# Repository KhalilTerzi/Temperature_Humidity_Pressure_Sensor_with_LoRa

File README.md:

# Temperature_Humidity_Pressure_Sensor_with_LoRa
Intelligent Sensor Connected with LoRa

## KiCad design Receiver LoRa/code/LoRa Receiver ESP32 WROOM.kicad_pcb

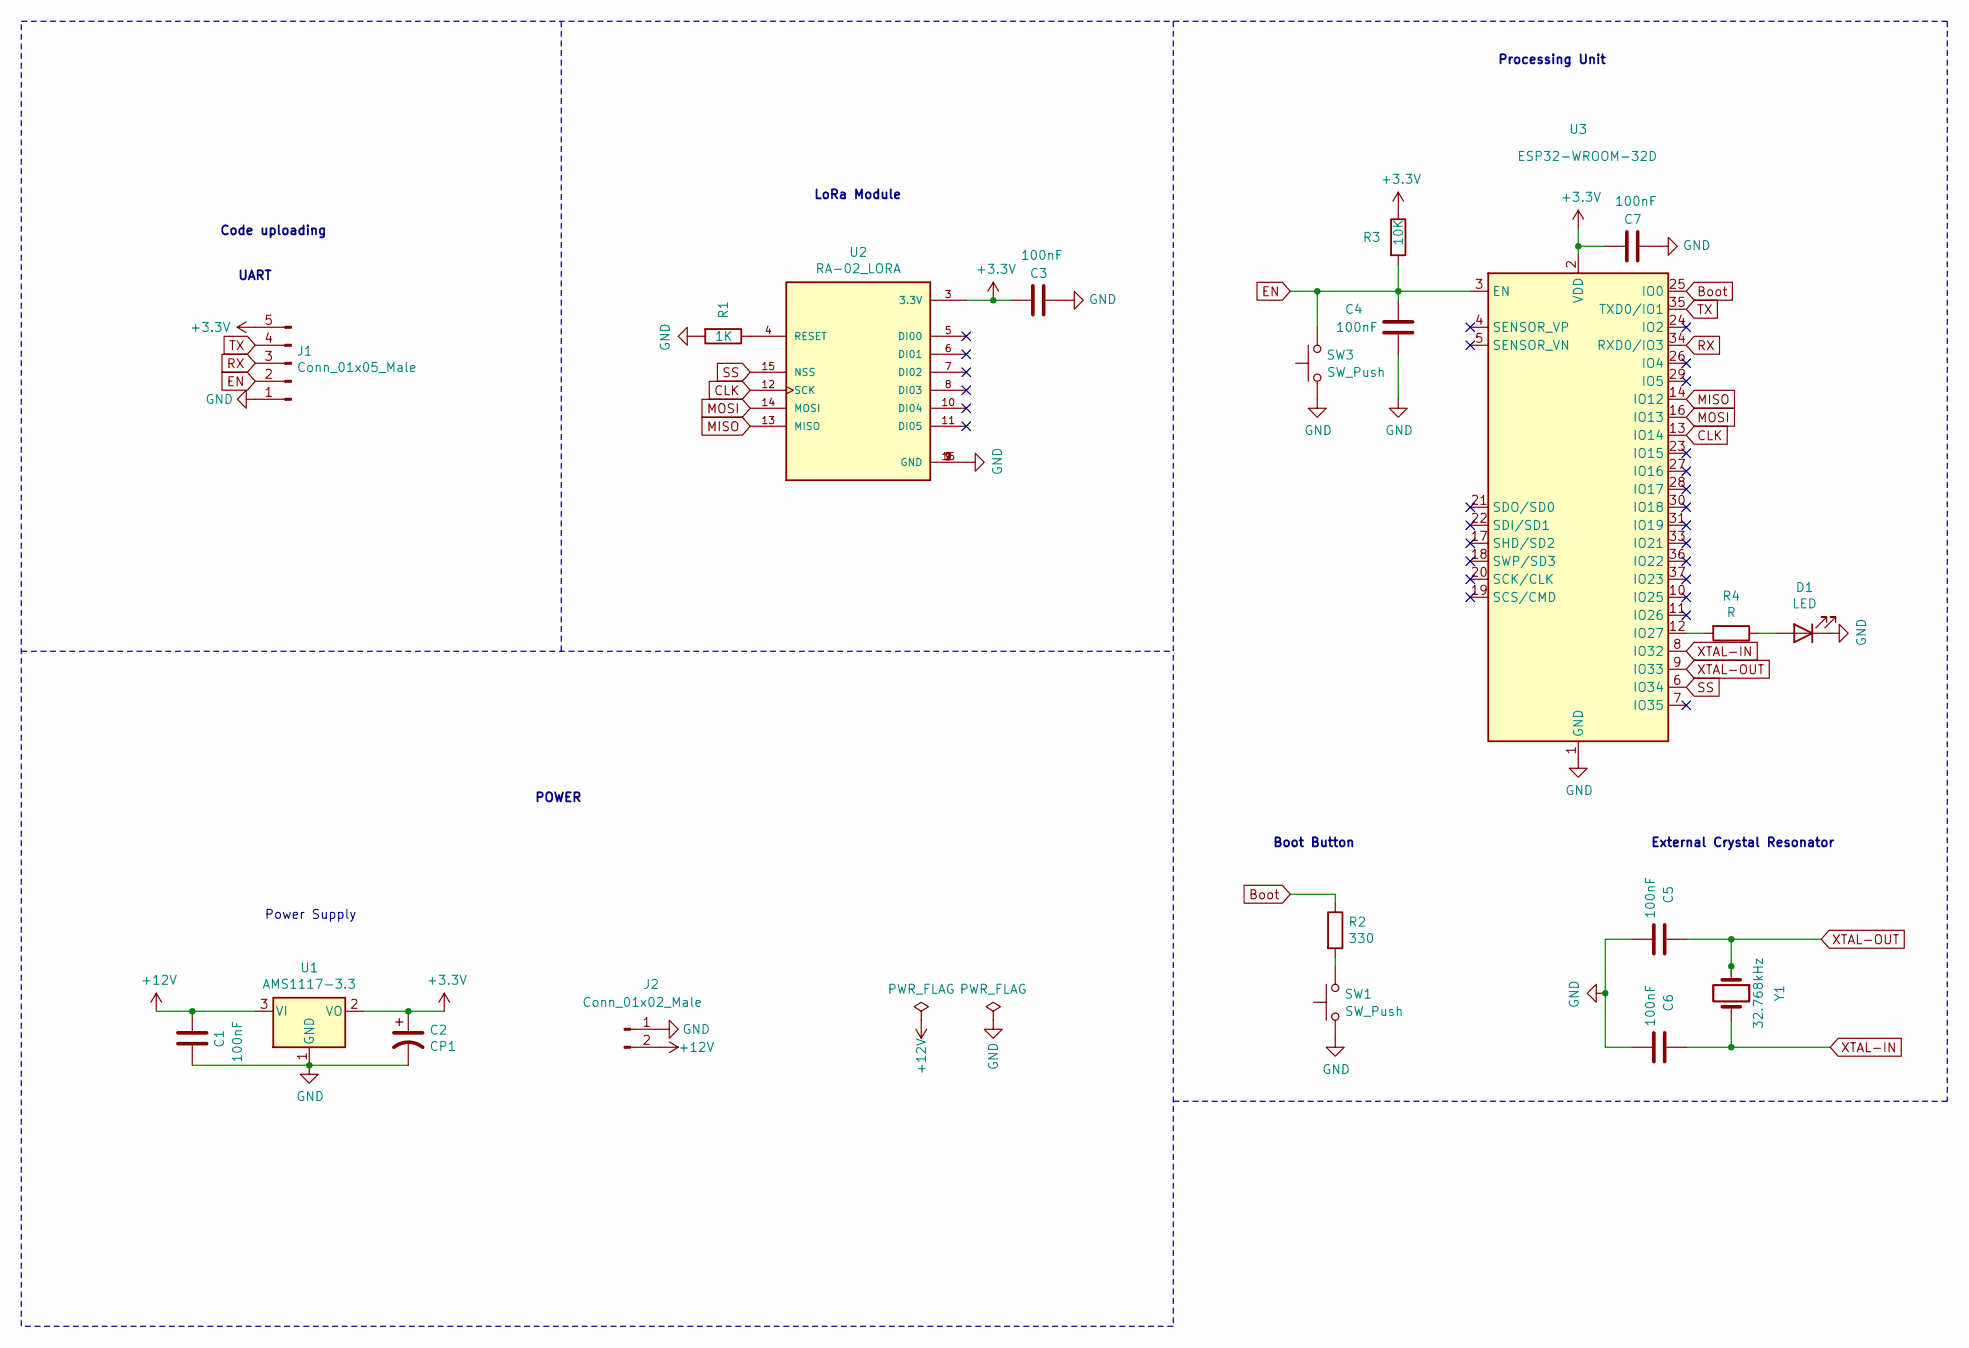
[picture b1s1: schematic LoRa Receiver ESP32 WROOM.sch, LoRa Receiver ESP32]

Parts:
C1: 100nF; C_0603_1608Metric_Pad1.08x0.95mm_HandSolder
C2: CP1; C_0603_1608Metric
C3, C4, C7: 100nF; C_0402_1005Metric
C5, C6: 100nF; C_0201_0603Metric
D1: LED; LED_0402_1005Metric
J1: Conn_01x05_Male; PinHeader_1x05_P2.54mm_Vertical
J2: Conn_01x02_Male; JST_EH_S2B-EH_1x02_P2.50mm_Horizontal
R1: 1K; R_0402_1005Metric
R2: 330; R_0402_1005Metric
R3: 10K; R_0402_1005Metric
R4: R; R_0402_1005Metric
SW1, SW3: SW_Push; SW_SPST_TL3342
U1: AMS1117-3.3; SOT-223-3_TabPin2
U2: RA-02_LORA; MODULE_RA-02_LORA
U3: ESP32-WROOM-32D; ESP32-WROOM-32
Y1: 32.768kHz; Crystal_SMD_3215-2Pin_3.2x1.5mm

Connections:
+3V3: C2.1, C3.2, C7.2, J1.5, R3.1, U1.2 (VO), U2.3 (3.3V), U3.2 (VDD)
+12V: C1.2, J2.2, U1.3 (VI)
Boot: R2.1, U3.25 (IO0)
CLK: U2.12 (SCK), U3.13 (IO14)
EN: C4.1, J1.2, R3.2, SW3.2, U3.3 (EN)
GND: C1.1, C2.2, C3.1, C4.2, C5.2, C6.2, C7.1, D1.1 (K), J1.1, J2.1, R1.2, SW1.1, SW3.1, U1.1 (GND), U2.1 (GND), U2.2 (GND), U2.9 (GND), U2.16 (GND), U3.1 (GND), U3.15 (GND), U3.38 (GND), U3.39 (GND)
MISO: U2.13 (MISO), U3.14 (IO12)
MOSI: U2.14 (MOSI), U3.16 (IO13)
unnamed: D1.2 (A), R4.1
unnamed: R1.1, U2.4 (RESET)
unnamed: R2.2, SW1.2
unnamed: R4.2, U3.12 (IO27)
RX: J1.3, U3.34 (RXD0/IO3)
SS: U2.15 (NSS), U3.6 (IO34)
TX: J1.4, U3.35 (TXD0/IO1)
XTAL-IN: C6.1, U3.8 (IO32), Y1.2
XTAL-OUT: C5.1, U3.9 (IO33), Y1.1

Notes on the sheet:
Processing Unit
External Crystal Resonator
LoRa Module
POWER
Power Supply
Boot Button
UART
Code uploading

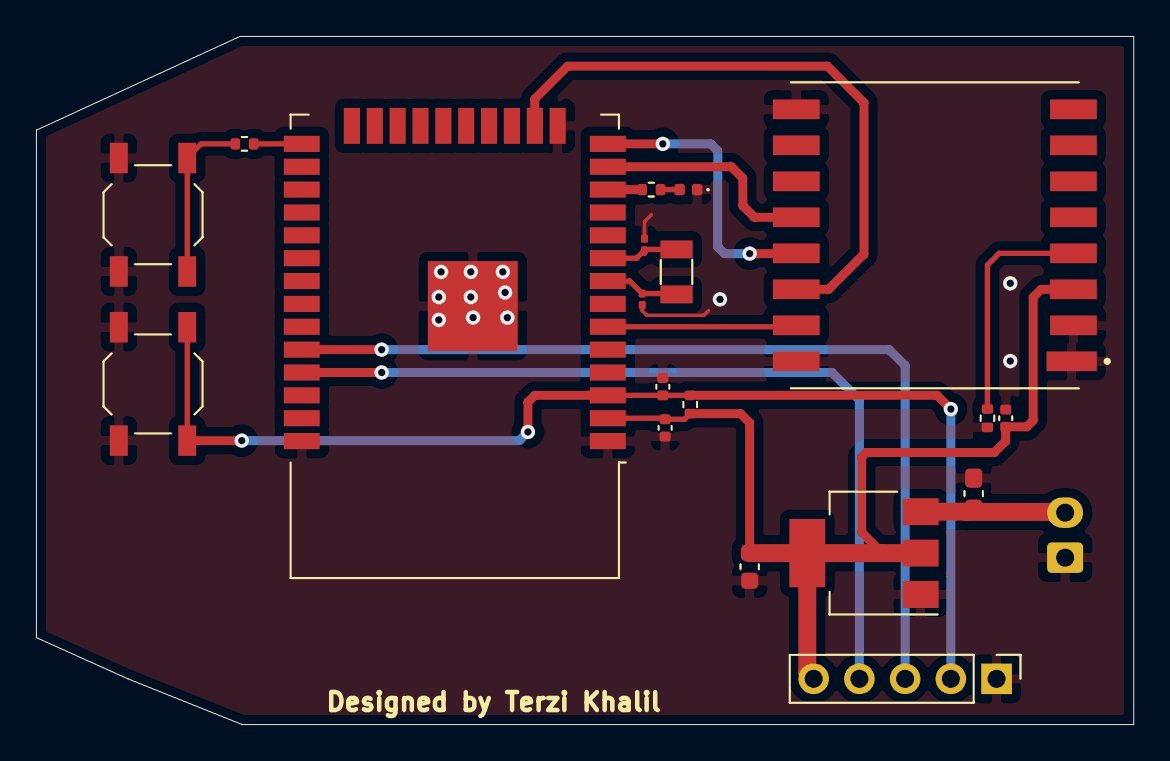
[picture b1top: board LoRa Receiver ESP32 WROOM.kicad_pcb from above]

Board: 2 copper layers, 61.0 x 38.2 mm, 20 parts (1 on the bottom side), 17 nets.

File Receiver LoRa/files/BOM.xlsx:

Ref | Val | Footprint | LCSC Part
C1 | 100nF | Capacitor_SMD:C_0603_1608Metric_Pad1.08x0.95mm_HandSolder | C83054
C2 | CP1 | Capacitor_SMD:C_0603_1608Metric | C83054
C3 | 100nF | Capacitor_SMD:C_0402_1005Metric | C1525
C4 | 100nF | Capacitor_SMD:C_0402_1005Metric | C1525
C7 | 100nF | Capacitor_SMD:C_0402_1005Metric | C1525
C5 | 100nF | Capacitor_SMD:C_0201_0603Metric | C1555
C6 | 100nF | Capacitor_SMD:C_0201_0603Metric | C1555
D1 | LED | LED_SMD:LED_0402_1005Metric | C165977
R1 | 1K | Resistor_SMD:R_0402_1005Metric | C11702
R2 | 330 | Resistor_SMD:R_0402_1005Metric | C25091
R3 | 10K | Resistor_SMD:R_0402_1005Metric | C25744
R4 | 220 | Resistor_SMD:R_0402_1005Metric | C25091
SW1, SW3 | SW_Push | Button_Switch_SMD:SW_SPST_TL3342
U1 | AMS1117-3.3 | Package_TO_SOT_SMD:SOT-223-3_TabPin2 | C6186
U2 | RA-02_LORA | footprint:MODULE_RA-02_LORA | C90039
U3 | ESP32-WROOM-32D | RF_Module:ESP32-WROOM-32 | C473012
Y1 | 32.768kHz | Crystal:Crystal_SMD_3215-2Pin_3.2x1.5mm | C32346

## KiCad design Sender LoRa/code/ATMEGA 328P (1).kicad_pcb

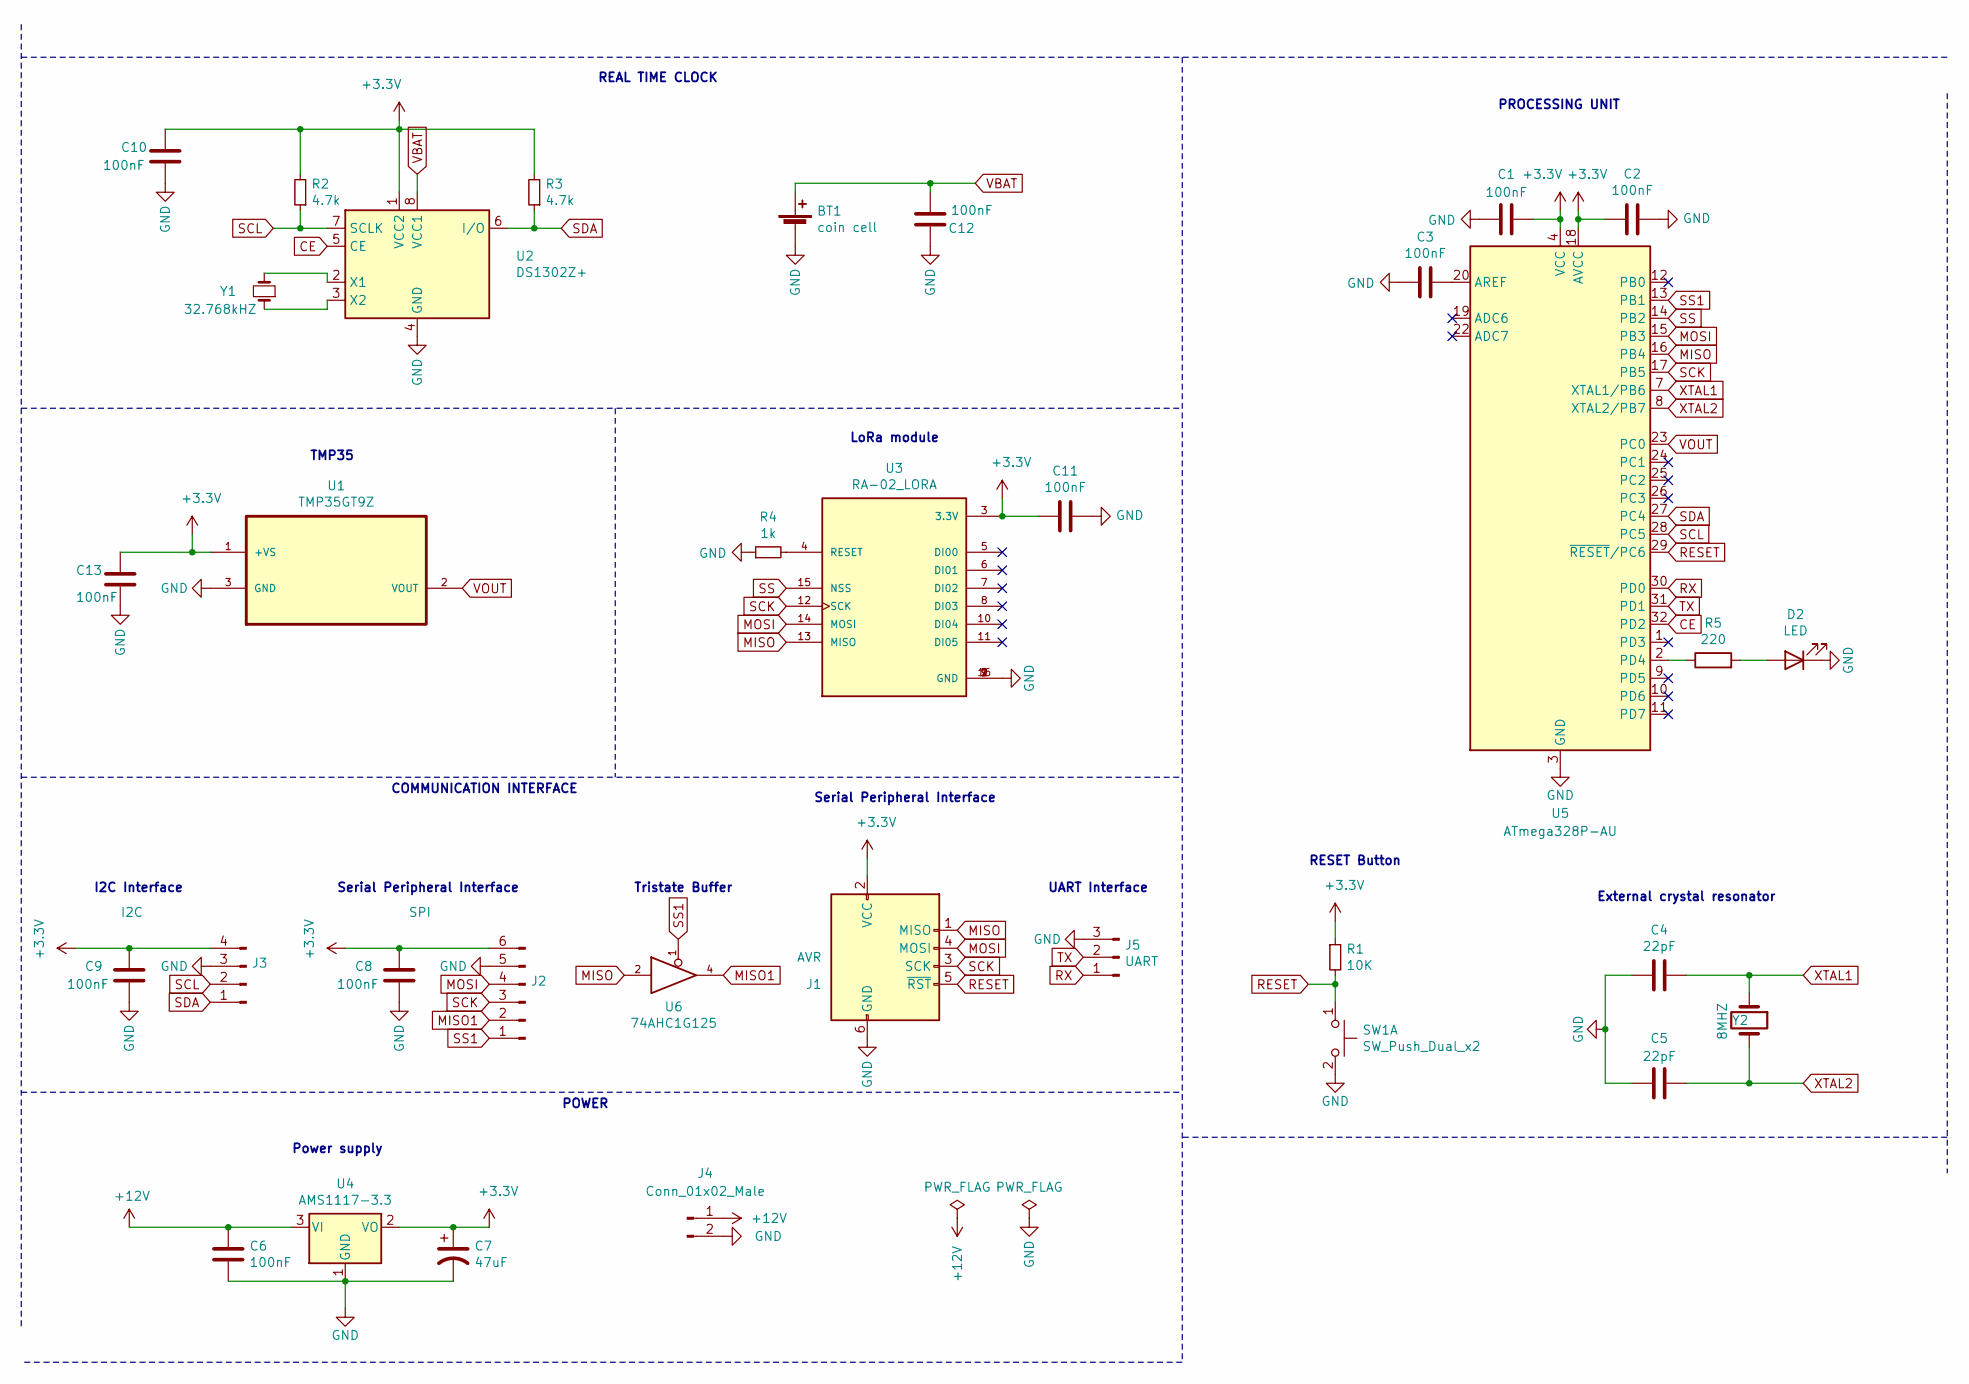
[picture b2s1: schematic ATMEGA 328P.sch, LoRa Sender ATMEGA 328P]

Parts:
BT1: coin cell; CR12202
C1, C2, C3, C6, C8, C9, C10, C11, C12, C13: 100nF; C_0402_1005Metric
C4, C5: 22pF; C_0402_1005Metric
C7: 47uF; C_0402_1005Metric
D2: LED; LED_0402_1005Metric
J1: AVR; PinHeader_2x03_P2.54mm_Vertical
J2: SPI; PinHeader_1x06_P2.54mm_Vertical
J3: I2C; PinHeader_1x04_P2.54mm_Vertical
J4: Conn_01x02_Male; JST_EH_S2B-EH_1x02_P2.50mm_Horizontal
J5: UART; PinHeader_1x03_P2.54mm_Vertical
R1: 10K; R_0402_1005Metric
R2, R3: 4.7k; R_0402_1005Metric
R4: 1k; R_0402_1005Metric
R5: 220; R_0402_1005Metric
SW1: SW_Push_Dual_x2; SW_SPST_TL3342
U1: TMP35GT9Z; TO127P254X533-3P; MPN TMP35GT9Z
U2: DS1302Z+; SOIC-8_3.9x4.9mm_P1.27mm
U3: RA-02_LORA; MODULE_RA-02_LORA
U4: AMS1117-3.3; SOT-223-3_TabPin2
U5: ATmega328P-AU; TQFP-32_7x7mm_P0.8mm
U6: 74AHC1G125; SOT-353_SC-70-5
Y1: 32.768kHZ; Crystal_SMD_3215-2Pin_3.2x1.5mm
Y2: 8MHZ; Crystal_SMD_5032-2Pin_5.0x3.2mm

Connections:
+3V3: C1.1, C2.2, C7.1, C8.1, C9.1, C10.1, C11.2, C13.1, J1.2 (VCC), J2.6, J3.4, R1.1, R2.2, R3.2, U1.1 (+VS), U2.1 (VCC2), U3.3 (3.3V), U4.2 (VO), U5.4 (VCC), U5.6 (VCC), U5.18 (AVCC)
+12V: C6.1, J4.1, U4.3 (VI)
CE: U2.5 (CE), U5.32 (PD2)
GND: BT1.2 (-), C1.2, C2.1, C3.2, C4.2, C5.2, C6.2, C7.2, C8.2, C9.2, C10.2, C11.1, C12.1, C13.2, D2.1 (K), J1.6 (GND), J2.5, J3.3, J4.2, J5.3, R4.1, SW1.2 (D), U1.3 (GND), U2.4 (GND), U3.1 (GND), U3.2 (GND), U3.9 (GND), U3.16 (GND), U4.1 (GND), U5.3 (GND), U5.5 (GND), U5.21 (GND), U6.3 (GND)
MISO: J1.1 (MISO), U3.13 (MISO), U5.16 (PB4), U6.2
MISO1: J2.2, U6.4
MOSI: J1.4 (MOSI), J2.4, U3.14 (MOSI), U5.15 (PB3)
unnamed: C3.1, U5.20 (AREF)
unnamed: D2.2 (A), R5.2
unnamed: R4.2, U3.4 (RESET)
unnamed: R5.1, U5.2 (PD4)
unnamed: U2.2 (X1), Y1.2
unnamed: U2.3 (X2), Y1.1
RESET: J1.5 (~RST), R1.2, SW1.1 (C), U5.29 (~RESET~/PC6)
RX: J5.1, U5.30 (PD0)
SCK: J1.3 (SCK), J2.3, U3.12 (SCK), U5.17 (PB5)
SCL: J3.2, R2.1, U2.7 (SCLK), U5.28 (PC5)
SDA: J3.1, R3.1, U2.6 (I/O), U5.27 (PC4)
SS: U3.15 (NSS), U5.14 (PB2)
SS1: J2.1, U5.13 (PB1), U6.1
TX: J5.2, U5.31 (PD1)
VBAT: BT1.1 (+), C12.2, U2.8 (VCC1)
VOUT: U1.2 (VOUT), U5.23 (PC0)
XTAL1: C4.1, U5.7 (XTAL1/PB6), Y2.1; also elsewhere on the board
XTAL2: C5.1, U5.8 (XTAL2/PB7), Y2.2; also elsewhere on the board

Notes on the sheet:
PROCESSING UNIT
External crystal resonator
Power supply
POWER
Serial Peripheral Interface
I2C Interface
COMMUNICATION INTERFACE
LoRa module
TMP35
REAL TIME CLOCK
UART Interface
RESET Button
Tristate Buffer

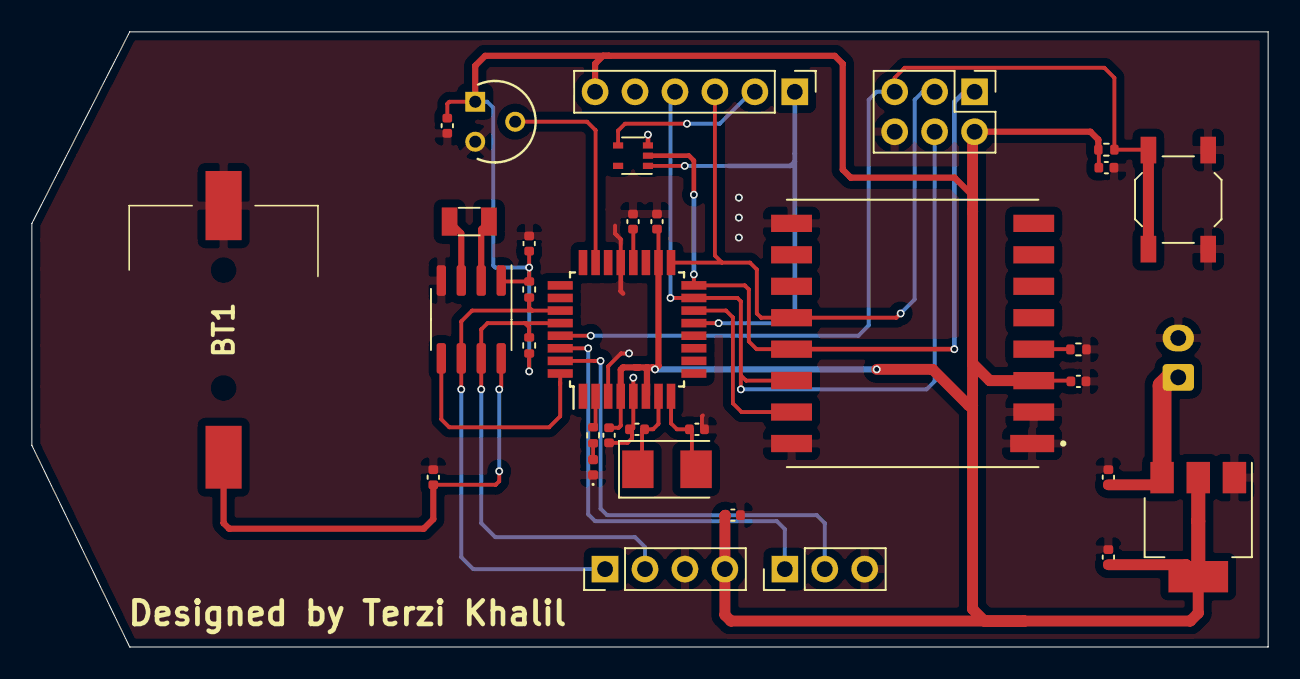
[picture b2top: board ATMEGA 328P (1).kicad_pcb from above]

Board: 2 copper layers, 78.6 x 39.1 mm, 34 parts (1 on the bottom side), 25 nets.

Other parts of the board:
8MHZ1: Crystal; Crystal_SMD_5032-2Pin_5.0x3.2mm

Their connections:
XTAL1: 8MHZ1.1; also elsewhere on the board
XTAL2: 8MHZ1.2; also elsewhere on the board

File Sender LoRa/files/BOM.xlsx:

Ref | Val | Footprint | LCSC Part
BT1 | coin cell | CR1220-2:CR12202 | C969906
C1 | 100nF | Capacitor_SMD:C_0402_1005Metric | C1525
C2 | 100nF | Capacitor_SMD:C_0402_1005Metric | C1525
C3 | 100nF | Capacitor_SMD:C_0402_1005Metric | C1525
C6 | 100nF | Capacitor_SMD:C_0402_1005Metric | C1525
C8 | 100nF | Capacitor_SMD:C_0402_1005Metric | C1525
C9 | 100nF | Capacitor_SMD:C_0402_1005Metric | C1525
C10 | 100nF | Capacitor_SMD:C_0402_1005Metric | C1525
C11 | 100nF | Capacitor_SMD:C_0402_1005Metric | C1525
C12 | 100nF | Capacitor_SMD:C_0402_1005Metric | C1525
C13 | 100nF | Capacitor_SMD:C_0402_1005Metric | C1525
C4 | 22pF | Capacitor_SMD:C_0201_0603Metric | C1555
C5 | 22pF | Capacitor_SMD:C_0201_0603Metric | C1555
C7 | 47uF | Capacitor_SMD:C_0402_1005Metric | C1525
D2 | LED | LED_SMD:LED_0402_1005Metric | C165977
R1 | 10K | Resistor_SMD:R_0402_1005Metric | C25744
R2 | 4.7k | Resistor_SMD:R_0402_1005Metric | C25900
R3 | 4.7k | Resistor_SMD:R_0402_1005Metric | C25900
R4 | 1k | Resistor_SMD:R_0402_1005Metric | C11702
R5 | 220 | Resistor_SMD:R_0402_1005Metric | C25091
SW1 | SW_Push_Dual_x2 | Button_Switch_SMD:SW_SPST_TL3342
U1 | TMP35GT9Z | footprint2:TO127P254X533-3P | C147943
U2 | DS1302Z+ | Package_SO:SOIC-8_3.9x4.9mm_P1.27mm | C8959
U3 | RA-02_LORA | footprint:MODULE_RA-02_LORA | C90039
U4 | AMS1117-3.3 | Package_TO_SOT_SMD:SOT-223-3_TabPin2 | C6186
U5 | ATmega328P-AU | Package_QFP:TQFP-32_7x7mm_P0.8mm | C14877
U6 | 74AHC1G125 | Package_TO_SOT_SMD:SOT-353_SC-70-5 | C507857
Y1 | 32.768kHZ | Crystal:Crystal_SMD_3215-2Pin_3.2x1.5mm | C32346
Y2 | 8MHZ | Crystal:Crystal_SMD_5032-2Pin_5.0x3.2mm | C115962

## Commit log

2021-12-14 1st commit
